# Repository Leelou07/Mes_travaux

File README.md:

# enseignement
Hello ! L'objectif est de partager les différents cours, notes et ressources que j'ai pu créer :)

ATTENTION !!!

Tous les contenus partagés dans ce répo a pour unique visé l'apprentissage. Je ne me tiens pas responsable de potentielle mauvaise utilisation!

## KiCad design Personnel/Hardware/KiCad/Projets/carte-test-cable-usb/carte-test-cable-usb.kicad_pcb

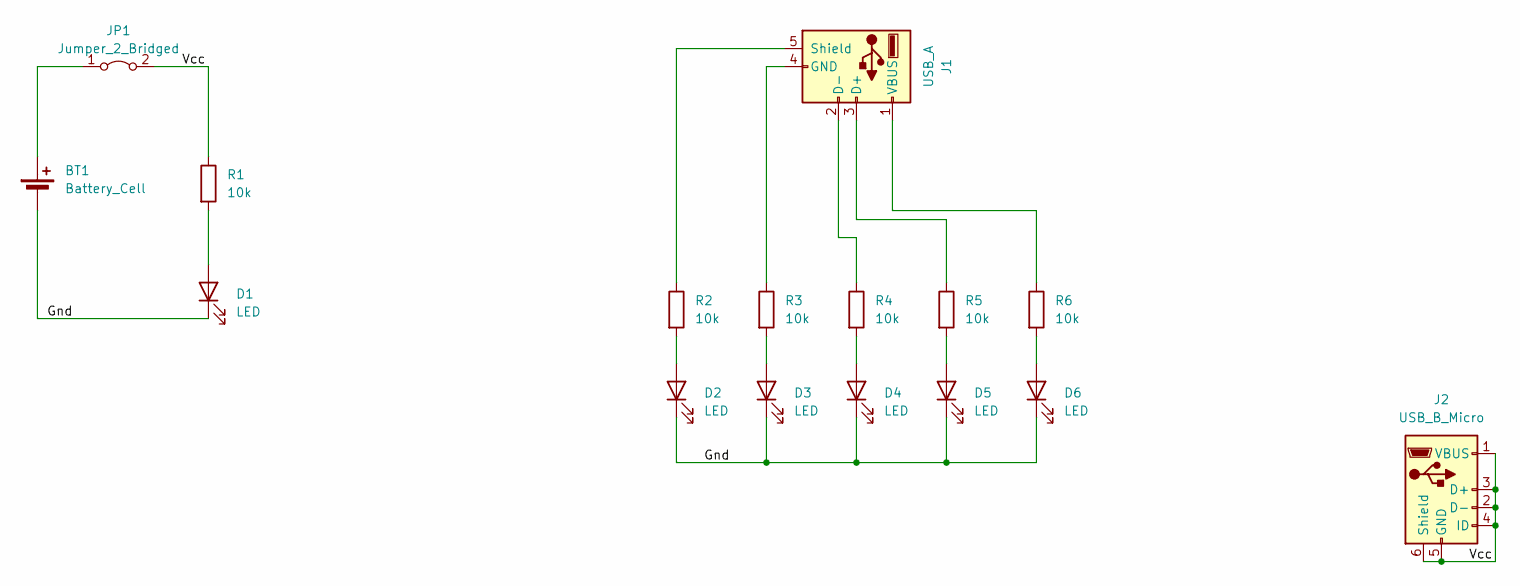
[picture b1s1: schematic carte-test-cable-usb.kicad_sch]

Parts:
BT1: Battery_Cell; BatteryHolder_Keystone_3002_1x2032
D1, D2, D3, D4, D5, D6: LED; LED_0603_1608Metric_Pad1.05x0.95mm_HandSolder
J1: USB_A; USB_A_Molex_67643_Horizontal
J2: USB_B_Micro; USB_Micro-B_Amphenol_10118194_Horizontal
JP1: Jumper_2_Bridged; SW_SPST_B3U-3000P
R1, R2, R3, R4, R5, R6: 10k; R_0603_1608Metric_Pad0.98x0.95mm_HandSolder

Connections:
/Gnd: BT1.2 (-), D1.1 (K), D2.1 (K), D3.1 (K), D4.1 (K), D5.1 (K), D6.1 (K)
/Vcc: J2.1 (VBUS), J2.2 (D-), J2.3 (D+), J2.4 (ID), J2.5 (GND), J2.6 (Shield), JP1.2 (B), R1.1
unnamed: BT1.1 (+), JP1.1 (A)
unnamed: D1.2 (A), R1.2
unnamed: D2.2 (A), R2.2
unnamed: D3.2 (A), R3.2
unnamed: D4.2 (A), R4.2
unnamed: D5.2 (A), R5.2
unnamed: D6.2 (A), R6.2
unnamed: J1.3 (D+), R5.1
unnamed: J1.2 (D-), R4.1
unnamed: J1.4 (GND), R3.1
unnamed: J1.5 (Shield), R2.1
unnamed: J1.1 (VBUS), R6.1

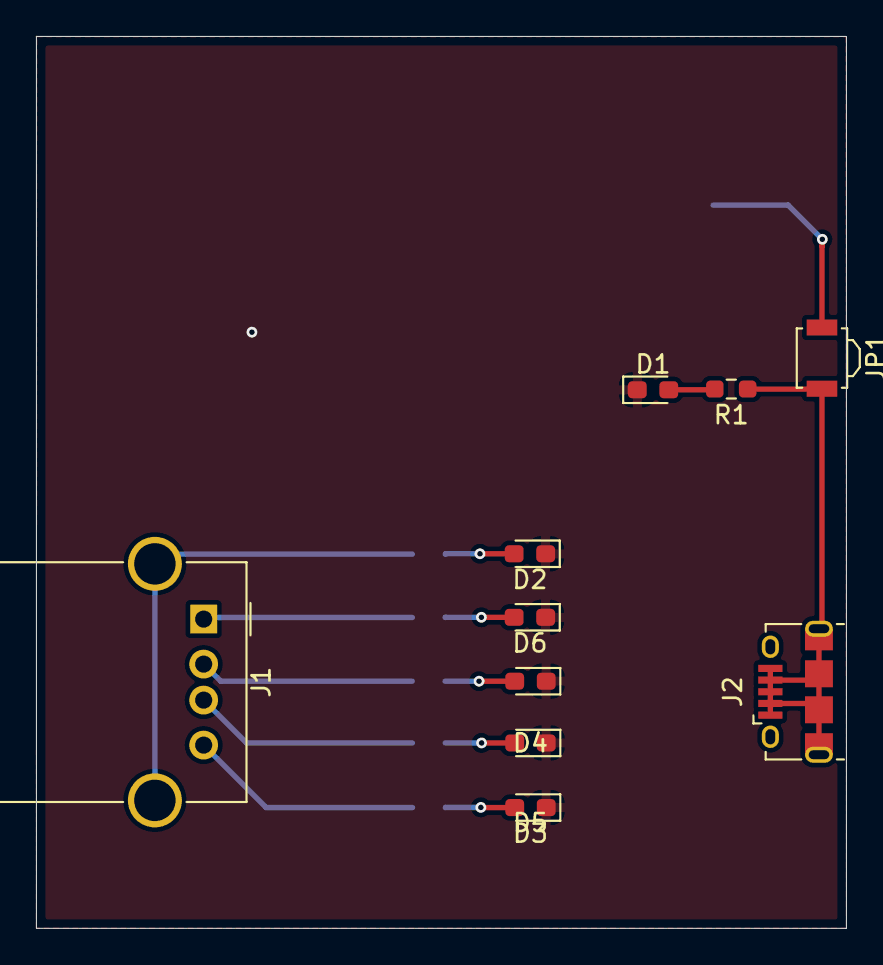
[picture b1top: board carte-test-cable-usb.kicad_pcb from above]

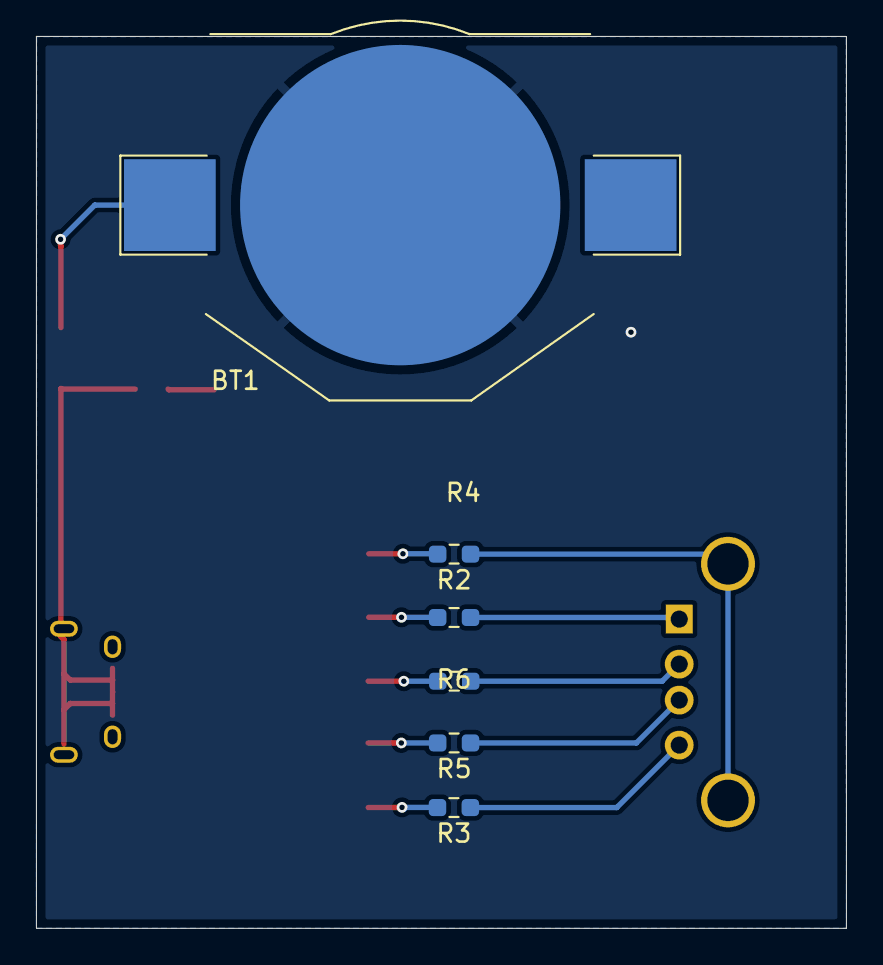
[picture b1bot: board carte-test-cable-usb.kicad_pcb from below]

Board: 2 copper layers, 45.0 x 49.6 mm, 16 parts (6 on the bottom side), 14 nets.

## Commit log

2023-11-25 projet_hardware
    rajout de la totalité du projet hardware fait en B2 - novembre
2023-11-25 modification chemin accès projet hardware
2023-11-25 ajout des projets B1
2023-11-25 Update README.md
    warning add
2023-11-25 ajout projets 1-2-3 B2
2023-12-15 Add Project 5 and 6
2023-12-15 Ajout des derniers fichiers du projet 5 & du Readme afin de comprendre leurs fonctionnement
2023-12-15 Ajout des synthèses en anglais
2023-12-15 Ajout des travaux lors de la semaine d'immersion
2023-12-15 ajout d'un readme et modification emplacement travail préparatoire
2023-12-17 Add firt version of zip brute force tool
2023-12-20 add new files
    Hardware -> BadUSB (GetRickRoll)
    B2 -> Tableau NIS VS NIS2
2023-12-20 Réorganisation
2023-12-25 Add obisidian
2024-01-11 add 2 new WU
    Starting point HTB Meow/Fawn
2024-01-11 move screen into assets folder
2024-01-11 add 2nd et 3 week of project 6
2024-01-11 add first oral exam in B2
2024-01-12 add Dancing & Reddemer
    Starting point HTB
2024-01-12 Rajout éléments de révision S1 B2
2024-01-12 ajout lien qcm hardware s1 b2
2024-01-12 re organise exam training
2024-01-13 add explosion, mongo
2024-01-29 programme hackday & script py hex to text
2024-01-31 hackropole crypto chall
2024-02-15 chqll ouverture club hardware
2024-03-02 projet hardware PCB
